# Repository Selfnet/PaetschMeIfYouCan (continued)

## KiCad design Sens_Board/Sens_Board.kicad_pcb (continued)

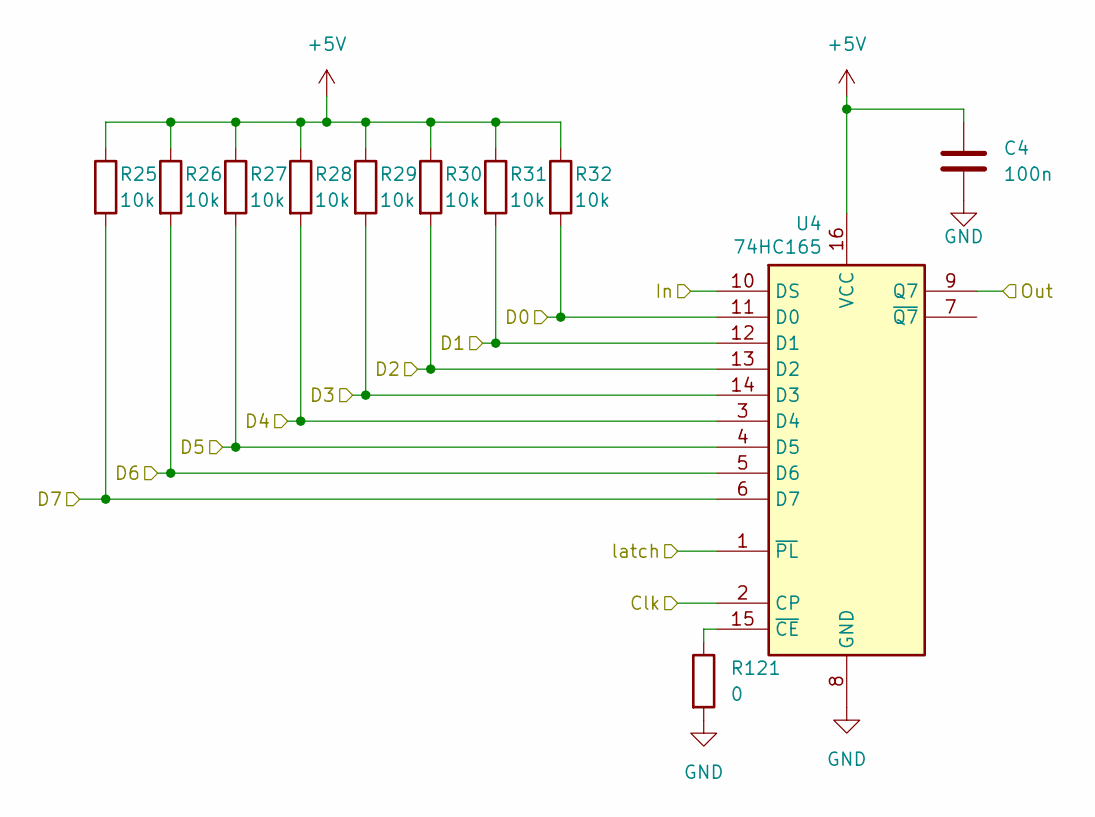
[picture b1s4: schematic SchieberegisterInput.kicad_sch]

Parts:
C4: 100n; C_0402_1005Metric
R25, R26, R27, R28, R29, R30, R31, R32: 10k; R_0402_1005Metric
R121: 0; R_0402_1005Metric
U4: 74HC165; SOIC-16_4.55x10.3mm_P1.27mm

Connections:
+5V: C4.1, R25.1, R26.1, R27.1, R28.1, R29.1, R30.1, R31.1, R32.1, U4.16 (VCC); also elsewhere on the board
/RJ45/SchieberegisterInput/D0: R32.2, U4.11 (D0); also elsewhere on the board
/RJ45/SchieberegisterInput/D1: R31.2, U4.12 (D1); also elsewhere on the board
/RJ45/SchieberegisterInput/D2: R30.2, U4.13 (D2); also elsewhere on the board
/RJ45/SchieberegisterInput/D3: R29.2, U4.14 (D3); also elsewhere on the board
/RJ45/SchieberegisterInput/D4: R28.2, U4.3 (D4); also elsewhere on the board
/RJ45/SchieberegisterInput/D5: R27.2, U4.4 (D5); also elsewhere on the board
/RJ45/SchieberegisterInput/D6: R26.2, U4.5 (D6); also elsewhere on the board
/RJ45/SchieberegisterInput/D7: R25.2, U4.6 (D7); also elsewhere on the board
/RJ45/SchieberegisterInput/Out: U4.9 (Q7); also elsewhere on the board
Data_Clk: U4.2 (CP); also elsewhere on the board
Data_Input: U4.10 (DS); also elsewhere on the board
Data_Latch: U4.1 (~PL); also elsewhere on the board
GND: C4.2, R121.2, U4.8 (GND); also elsewhere on the board
unnamed: R121.1, U4.15 (~CE)

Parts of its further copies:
C13, C22, C31, C40, C49, C58, C67, C76, C85, C94, C103: 100n; C_0402_1005Metric
R33, R34, R35, R36, R37, R38, R39, R40, R41, R42, R43, R44, R45, R46, R47, R48, R49, R50, R51, R52, R53, R54, R55, R56, R57, R58, R59, R60, R61, R62, R63, R64, R65, R66, R67, R68, R69, R70, R71, R72, R73, R74, R75, R76, R77, R78, R79, R80, R81, R82, R83, R84, R85, R86, R87, R88, R89, R90, R91, R92, R93, R94, R95, R96, R97, R98, R99, R100, R101, R102, R103, R104, R105, R106, R107, R108, R109, R110, R111, R112, R113, R114, R115, R116, R117, R118, R119, R120: 10k; R_0402_1005Metric
R122, R123, R124, R125, R126, R127, R128, R129, R130, R131, R132: 0; R_0402_1005Metric
U5, U6, U7, U8, U9, U10, U11, U12, U13, U14, U15: 74HC165; SOIC-16_4.55x10.3mm_P1.27mm

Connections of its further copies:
+5V: C13.1, C22.1, C31.1, C40.1, C49.1, C58.1, C67.1, C76.1, C85.1, C94.1, C103.1, R33.1, R34.1, R35.1, R36.1, R37.1, R38.1, R39.1, R40.1, R41.1, R42.1, R43.1, R44.1, R45.1, R46.1, R47.1, R48.1, R49.1, R50.1, R51.1, R52.1, R53.1, R54.1, R55.1, R56.1, R57.1, R58.1, R59.1, R60.1, R61.1, R62.1, R63.1, R64.1, R65.1, R66.1, R67.1, R68.1, R69.1, R70.1, R71.1, R72.1, R73.1, R74.1, R75.1, R76.1, R77.1, R78.1, R79.1, R80.1, R81.1, R82.1, R83.1, R84.1, R85.1, R86.1, R87.1, R88.1, R89.1, R90.1, R91.1, R92.1, R93.1, R94.1, R95.1, R96.1, R97.1, R98.1, R99.1, R100.1, R101.1, R102.1, R103.1, R104.1, R105.1, R106.1, R107.1, R108.1, R109.1, R110.1, R111.1, R112.1, R113.1, R114.1, R115.1, R116.1, R117.1, R118.1, R119.1, R120.1, U5.16 (VCC), U6.16 (VCC), U7.16 (VCC), U8.16 (VCC), U9.16 (VCC), U10.16 (VCC), U11.16 (VCC), U12.16 (VCC), U13.16 (VCC), U14.16 (VCC), U15.16 (VCC); also elsewhere on the board
/RJ45/SchieberegisterInput1/D0: R48.2, U5.11 (D0); also elsewhere on the board
/RJ45/SchieberegisterInput1/D1: R47.2, U5.12 (D1); also elsewhere on the board
/RJ45/SchieberegisterInput1/D2: R46.2, U5.13 (D2); also elsewhere on the board
/RJ45/SchieberegisterInput1/D3: R45.2, U5.14 (D3); also elsewhere on the board
/RJ45/SchieberegisterInput1/D4: R44.2, U5.3 (D4); also elsewhere on the board
/RJ45/SchieberegisterInput1/D5: R43.2, U5.4 (D5); also elsewhere on the board
/RJ45/SchieberegisterInput1/D6: R42.2, U5.5 (D6); also elsewhere on the board
/RJ45/SchieberegisterInput1/D7: R41.2, U5.6 (D7); also elsewhere on the board
/RJ45/SchieberegisterInput1/Out: U5.9 (Q7), U6.10 (DS)
/RJ45/SchieberegisterInput2/D0: R40.2, U6.11 (D0); also elsewhere on the board
/RJ45/SchieberegisterInput2/D1: R39.2, U6.12 (D1); also elsewhere on the board
/RJ45/SchieberegisterInput2/D2: R38.2, U6.13 (D2); also elsewhere on the board
/RJ45/SchieberegisterInput2/D3: R37.2, U6.14 (D3); also elsewhere on the board
/RJ45/SchieberegisterInput2/D4: R36.2, U6.3 (D4); also elsewhere on the board
/RJ45/SchieberegisterInput2/D5: R35.2, U6.4 (D5); also elsewhere on the board
/RJ45/SchieberegisterInput2/D6: R34.2, U6.5 (D6); also elsewhere on the board
/RJ45/SchieberegisterInput2/D7: R33.2, U6.6 (D7); also elsewhere on the board
/RJ45/SchieberegisterInput2/Out: U6.9 (Q7), U7.10 (DS)
/RJ45/SchieberegisterInput3/D0: R56.2, U7.11 (D0); also elsewhere on the board
/RJ45/SchieberegisterInput3/D1: R55.2, U7.12 (D1); also elsewhere on the board
/RJ45/SchieberegisterInput3/D2: R54.2, U7.13 (D2); also elsewhere on the board
/RJ45/SchieberegisterInput3/D3: R53.2, U7.14 (D3); also elsewhere on the board
/RJ45/SchieberegisterInput3/D4: R52.2, U7.3 (D4); also elsewhere on the board
/RJ45/SchieberegisterInput3/D5: R51.2, U7.4 (D5); also elsewhere on the board
/RJ45/SchieberegisterInput3/D6: R50.2, U7.5 (D6); also elsewhere on the board
/RJ45/SchieberegisterInput3/D7: R49.2, U7.6 (D7); also elsewhere on the board
/RJ45/SchieberegisterInput3/Out: U7.9 (Q7), U8.10 (DS)
/RJ45/SchieberegisterInput4/D0: R64.2, U8.11 (D0); also elsewhere on the board
/RJ45/SchieberegisterInput4/D1: R63.2, U8.12 (D1); also elsewhere on the board
/RJ45/SchieberegisterInput4/D2: R62.2, U8.13 (D2); also elsewhere on the board
/RJ45/SchieberegisterInput4/D3: R61.2, U8.14 (D3); also elsewhere on the board
/RJ45/SchieberegisterInput4/D4: R60.2, U8.3 (D4); also elsewhere on the board
/RJ45/SchieberegisterInput4/D5: R59.2, U8.4 (D5); also elsewhere on the board
/RJ45/SchieberegisterInput4/D6: R58.2, U8.5 (D6); also elsewhere on the board
/RJ45/SchieberegisterInput4/D7: R57.2, U8.6 (D7); also elsewhere on the board
/RJ45/SchieberegisterInput4/Out: U8.9 (Q7), U9.10 (DS)
/RJ45/SchieberegisterInput5/D0: R72.2, U9.11 (D0); also elsewhere on the board
/RJ45/SchieberegisterInput5/D1: R71.2, U9.12 (D1); also elsewhere on the board
/RJ45/SchieberegisterInput5/D2: R70.2, U9.13 (D2); also elsewhere on the board
/RJ45/SchieberegisterInput5/D3: R69.2, U9.14 (D3); also elsewhere on the board
/RJ45/SchieberegisterInput5/D4: R68.2, U9.3 (D4); also elsewhere on the board
/RJ45/SchieberegisterInput5/D5: R67.2, U9.4 (D5); also elsewhere on the board
/RJ45/SchieberegisterInput5/D6: R66.2, U9.5 (D6); also elsewhere on the board
/RJ45/SchieberegisterInput5/D7: R65.2, U9.6 (D7); also elsewhere on the board
/RJ45/SchieberegisterInput5/Out: U9.9 (Q7), U10.10 (DS)
/RJ45/SchieberegisterInput6/D0: R80.2, U10.11 (D0); also elsewhere on the board
/RJ45/SchieberegisterInput6/D1: R79.2, U10.12 (D1); also elsewhere on the board
/RJ45/SchieberegisterInput6/D2: R78.2, U10.13 (D2); also elsewhere on the board
/RJ45/SchieberegisterInput6/D3: R77.2, U10.14 (D3); also elsewhere on the board
/RJ45/SchieberegisterInput6/D4: R76.2, U10.3 (D4); also elsewhere on the board
/RJ45/SchieberegisterInput6/D5: R75.2, U10.4 (D5); also elsewhere on the board
/RJ45/SchieberegisterInput6/D6: R74.2, U10.5 (D6); also elsewhere on the board
/RJ45/SchieberegisterInput6/D7: R73.2, U10.6 (D7); also elsewhere on the board
/RJ45/SchieberegisterInput6/Out: U10.9 (Q7), U11.10 (DS)
/RJ45/SchieberegisterInput7/D0: R88.2, U11.11 (D0); also elsewhere on the board
/RJ45/SchieberegisterInput7/D1: R87.2, U11.12 (D1); also elsewhere on the board
/RJ45/SchieberegisterInput7/D2: R86.2, U11.13 (D2); also elsewhere on the board
/RJ45/SchieberegisterInput7/D3: R85.2, U11.14 (D3); also elsewhere on the board
/RJ45/SchieberegisterInput7/D4: R84.2, U11.3 (D4); also elsewhere on the board
/RJ45/SchieberegisterInput7/D5: R83.2, U11.4 (D5); also elsewhere on the board
/RJ45/SchieberegisterInput7/D6: R82.2, U11.5 (D6); also elsewhere on the board
/RJ45/SchieberegisterInput7/D7: R81.2, U11.6 (D7); also elsewhere on the board
/RJ45/SchieberegisterInput7/Out: U11.9 (Q7), U12.10 (DS)
/RJ45/SchieberegisterInput8/D0: R96.2, U12.11 (D0); also elsewhere on the board
/RJ45/SchieberegisterInput8/D1: R95.2, U12.12 (D1); also elsewhere on the board
/RJ45/SchieberegisterInput8/D2: R94.2, U12.13 (D2); also elsewhere on the board
/RJ45/SchieberegisterInput8/D3: R93.2, U12.14 (D3); also elsewhere on the board
/RJ45/SchieberegisterInput8/D4: R92.2, U12.3 (D4); also elsewhere on the board
/RJ45/SchieberegisterInput8/D5: R91.2, U12.4 (D5); also elsewhere on the board
/RJ45/SchieberegisterInput8/D6: R90.2, U12.5 (D6); also elsewhere on the board
/RJ45/SchieberegisterInput8/D7: R89.2, U12.6 (D7); also elsewhere on the board
/RJ45/SchieberegisterInput8/Out: U12.9 (Q7), U13.10 (DS)
/RJ45/SchieberegisterInput9/D0: R104.2, U13.11 (D0); also elsewhere on the board
/RJ45/SchieberegisterInput9/D1: R103.2, U13.12 (D1); also elsewhere on the board
/RJ45/SchieberegisterInput9/D2: R102.2, U13.13 (D2); also elsewhere on the board
/RJ45/SchieberegisterInput9/D3: R101.2, U13.14 (D3); also elsewhere on the board
/RJ45/SchieberegisterInput9/D4: R100.2, U13.3 (D4); also elsewhere on the board
/RJ45/SchieberegisterInput9/D5: R99.2, U13.4 (D5); also elsewhere on the board
/RJ45/SchieberegisterInput9/D6: R98.2, U13.5 (D6); also elsewhere on the board
/RJ45/SchieberegisterInput9/D7: R97.2, U13.6 (D7); also elsewhere on the board
/RJ45/SchieberegisterInput10/D0: R112.2, U14.11 (D0); also elsewhere on the board
/RJ45/SchieberegisterInput10/D1: R111.2, U14.12 (D1); also elsewhere on the board
/RJ45/SchieberegisterInput10/D2: R110.2, U14.13 (D2); also elsewhere on the board
/RJ45/SchieberegisterInput10/D3: R109.2, U14.14 (D3); also elsewhere on the board
/RJ45/SchieberegisterInput10/D4: R108.2, U14.3 (D4); also elsewhere on the board
/RJ45/SchieberegisterInput10/D5: R107.2, U14.4 (D5); also elsewhere on the board
/RJ45/SchieberegisterInput10/D6: R106.2, U14.5 (D6); also elsewhere on the board
/RJ45/SchieberegisterInput10/D7: R105.2, U14.6 (D7); also elsewhere on the board
/RJ45/SchieberegisterInput10/In: U13.9 (Q7), U14.10 (DS)
/RJ45/SchieberegisterInput10/Out: U14.9 (Q7), U15.10 (DS)
/RJ45/SchieberegisterInput11/D0: R120.2, U15.11 (D0); also elsewhere on the board
/RJ45/SchieberegisterInput11/D1: R119.2, U15.12 (D1); also elsewhere on the board
/RJ45/SchieberegisterInput11/D2: R118.2, U15.13 (D2); also elsewhere on the board
/RJ45/SchieberegisterInput11/D3: R117.2, U15.14 (D3); also elsewhere on the board
/RJ45/SchieberegisterInput11/D4: R116.2, U15.3 (D4); also elsewhere on the board
/RJ45/SchieberegisterInput11/D5: R115.2, U15.4 (D5); also elsewhere on the board
/RJ45/SchieberegisterInput11/D6: R114.2, U15.5 (D6); also elsewhere on the board
/RJ45/SchieberegisterInput11/D7: R113.2, U15.6 (D7); also elsewhere on the board
/RJ45/SchieberegisterInput/Out: U5.10 (DS); also elsewhere on the board
Data_Clk: U5.2 (CP), U6.2 (CP), U7.2 (CP), U8.2 (CP), U9.2 (CP), U10.2 (CP), U11.2 (CP), U12.2 (CP), U13.2 (CP), U14.2 (CP), U15.2 (CP); also elsewhere on the board
Data_Latch: U5.1 (~PL), U6.1 (~PL), U7.1 (~PL), U8.1 (~PL), U9.1 (~PL), U10.1 (~PL), U11.1 (~PL), U12.1 (~PL), U13.1 (~PL), U14.1 (~PL), U15.1 (~PL); also elsewhere on the board
Data_Output: U15.9 (Q7); also elsewhere on the board
GND: C13.2, C22.2, C31.2, C40.2, C49.2, C58.2, C67.2, C76.2, C85.2, C94.2, C103.2, R122.2, R123.2, R124.2, R125.2, R126.2, R127.2, R128.2, R129.2, R130.2, R131.2, R132.2, U5.8 (GND), U6.8 (GND), U7.8 (GND), U8.8 (GND), U9.8 (GND), U10.8 (GND), U11.8 (GND), U12.8 (GND), U13.8 (GND), U14.8 (GND), U15.8 (GND); also elsewhere on the board
unnamed: R123.1, U5.15 (~CE)
unnamed: R122.1, U6.15 (~CE)
unnamed: R124.1, U7.15 (~CE)
unnamed: R125.1, U8.15 (~CE)
unnamed: R126.1, U9.15 (~CE)
unnamed: R127.1, U10.15 (~CE)
unnamed: R128.1, U11.15 (~CE)
unnamed: R129.1, U12.15 (~CE)
unnamed: R130.1, U13.15 (~CE)
unnamed: R131.1, U14.15 (~CE)
unnamed: R132.1, U15.15 (~CE)

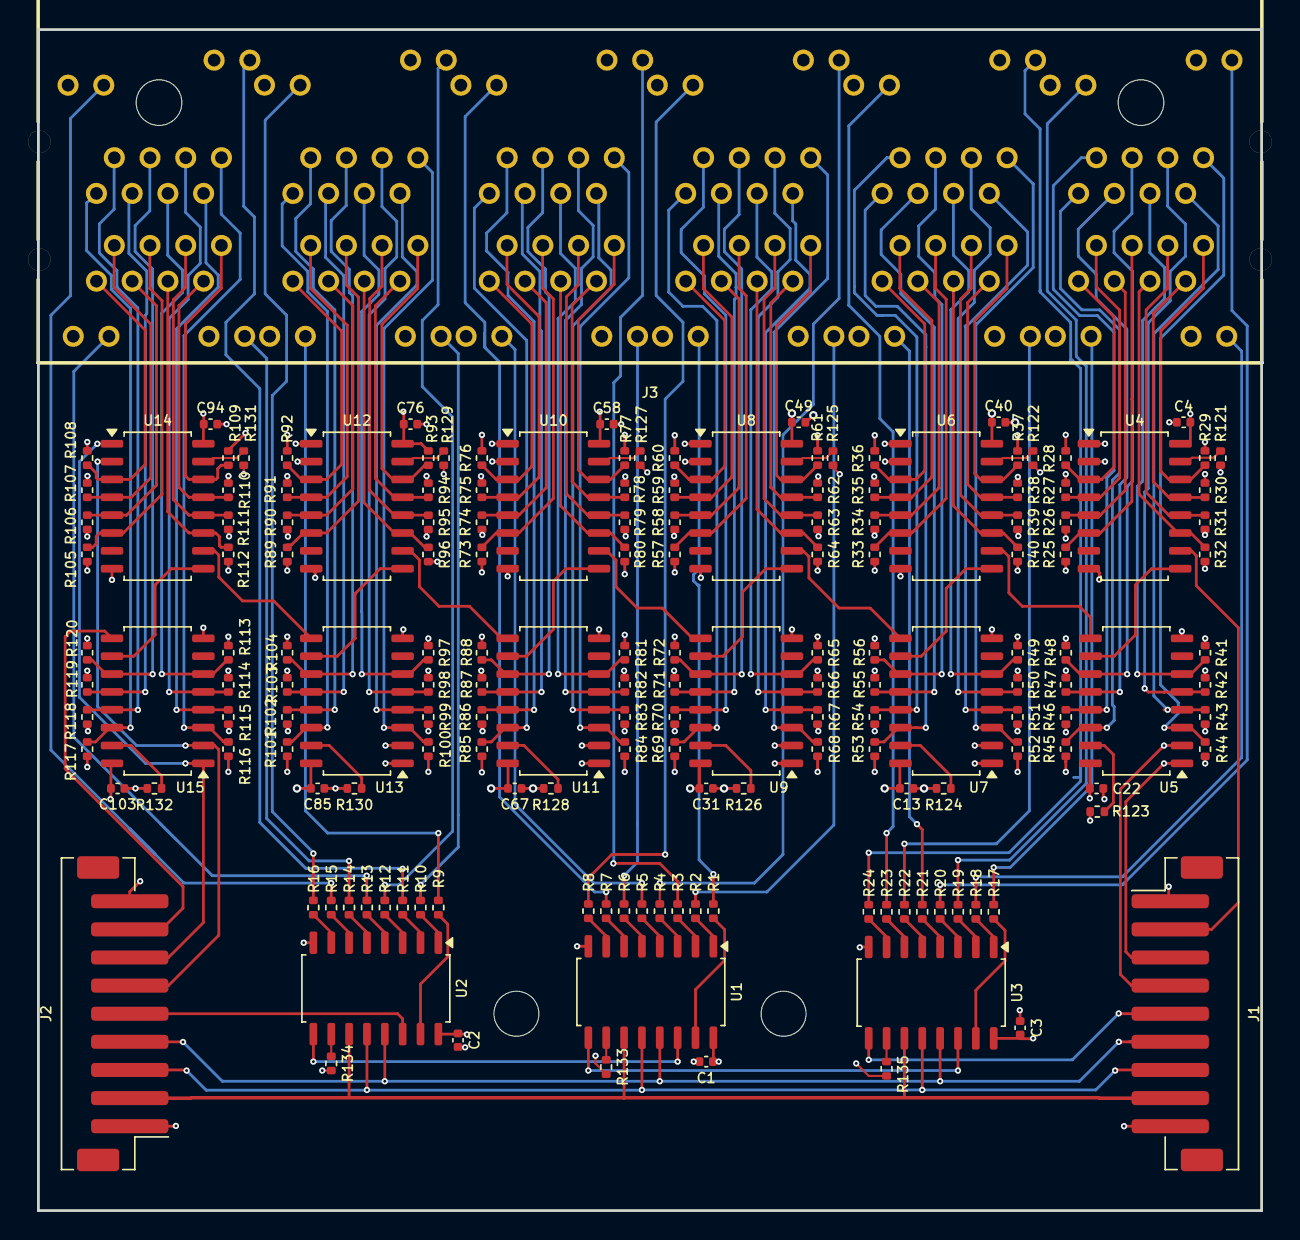
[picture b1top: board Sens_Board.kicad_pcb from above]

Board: 4 copper layers, 87.0 x 84.0 mm, 170 parts (0 on the bottom side), 183 nets.

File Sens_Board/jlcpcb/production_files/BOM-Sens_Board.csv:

Comment,Designator,Footprint,LCSC,Quantity
0,"R121,R122,R123,R124,R125,R126,R127,R128,R129,R130,R131,R132,R133,R134,R135",R_0402_1005Metric,C17168,15
100n,"C1,C103,C13,C2,C22,C3,C31,C4,C40,C49,C58,C67,C76,C85,C94",C_0402_1005Metric,C1525,15
10k,"R100,R101,R102,R103,R104,R105,R106,R107,R108,R109,R110,R111,R112,R113,R114,R115,R116,R117,R118,R119,R120,R25,R26,R27,R28,R29,R30,R31,R32,R33,R34,R35,R36,R37,R38,R39,R40,R41,R42,R43,R44,R45,R46,R47,R48,R49,R50,R51,R52,R53,R54,R55,R56,R57,R58,R59,R60,R61,R62,R63,R64,R65,R66,R67,R68,R69,R70,R71,R72,R73,R74,R75,R76,R77,R78,R79,R80,R81,R82,R83,R84,R85,R86,R87,R88,R89,R90,R91,R92,R93,R94,R95,R96,R97,R98,R99",R_0402_1005Metric,C25744,96
120,"R1,R10,R11,R12,R13,R14,R15,R16,R17,R18,R19,R2,R20,R21,R22,R23,R24,R3,R4,R5,R6,R7,R8,R9",R_0402_1005Metric,C25079,24
74HC165,"U10,U11,U12,U13,U14,U15,U4,U5,U6,U7,U8,U9",SOIC-16_4.55x10.3mm_P1.27mm,C5613,12
74HC595,"U1,U2,U3",SOIC-16_4.55x10.3mm_P1.27mm,C5947,3
Conn_01x09_Pin,"J1,J2",JST_PH_B9B-PH-SM4-TB_1x09-1MP_P2.00mm_Vertical,C5175301,2
~,J3,RJ45-TH_RJ45-TH_HC-RJ45-059D-2X6-2-04,C46261622,1

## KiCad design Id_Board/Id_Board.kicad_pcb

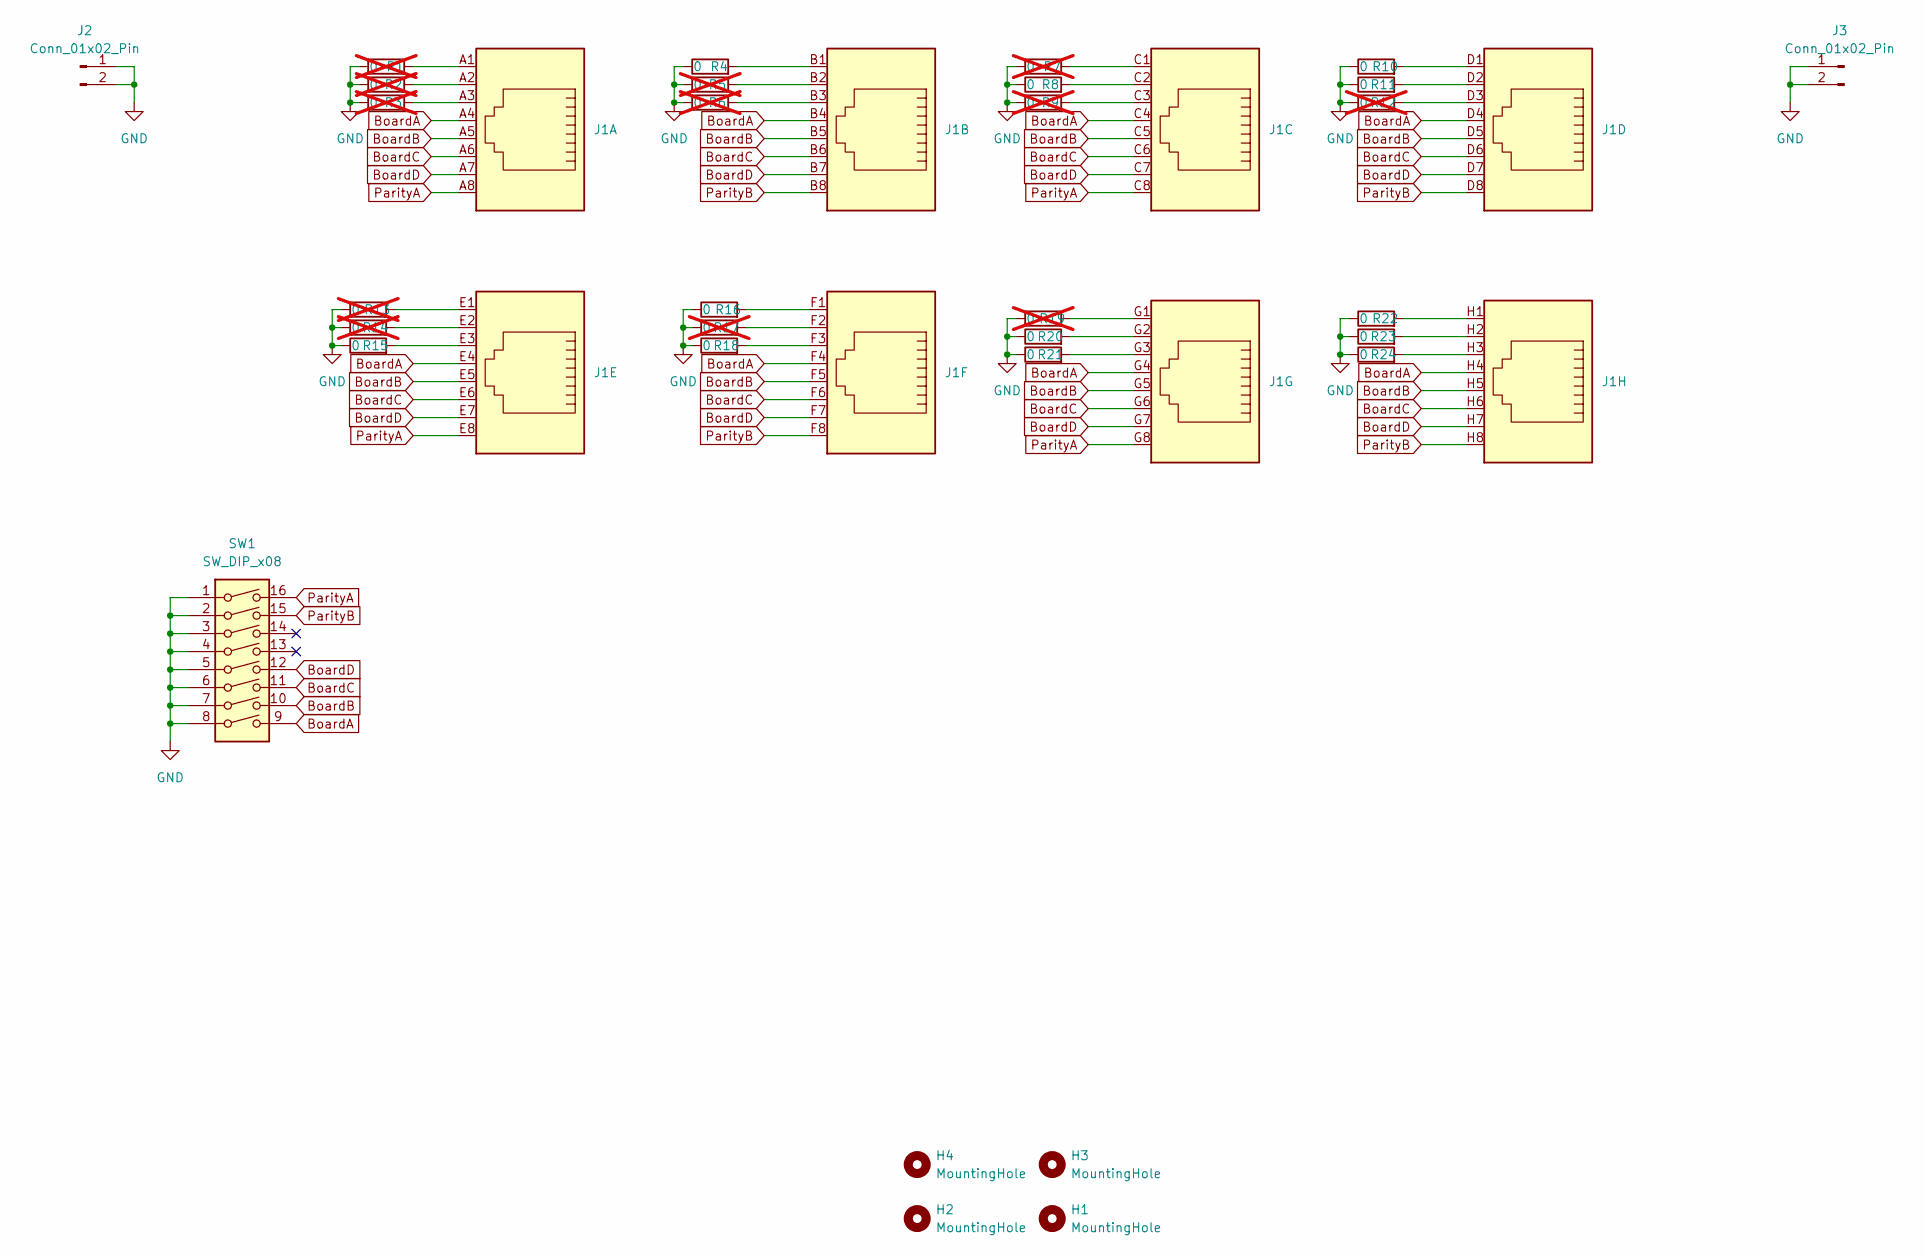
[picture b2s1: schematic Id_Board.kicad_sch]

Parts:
H1, H2, H3, H4: MountingHole; MountingHole_3.2mm_M3
J1: RJ45-TH_HC-WK88-H13-1X8-55QS_1
J2, J3: Conn_01x02_Pin; JST_PH_B2B-PH-SM4-TB_1x02-1MP_P2.00mm_Vertical
R1, R2, R3, R5, R6, R7, R9, R12, R13, R14, R17, R19: 0; R_0603_1608Metric; not fitted
R4, R8, R10, R11, R15, R16, R18, R20, R21, R22, R23, R24: 0; R_0603_1608Metric
SW1: SW_DIP_x08; SW-SMD_16P-L20.3-W6.0-P2.54-LS9.3-BL

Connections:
BoardA: J1.A4, J1.B4, J1.C4, J1.D4, J1.E4, J1.F4, J1.G4, J1.H4, SW1.9
BoardB: J1.A5, J1.B5, J1.C5, J1.D5, J1.E5, J1.F5, J1.G5, J1.H5, SW1.10
BoardC: J1.A6, J1.B6, J1.C6, J1.D6, J1.E6, J1.F6, J1.G6, J1.H6, SW1.11
BoardD: J1.A7, J1.B7, J1.C7, J1.D7, J1.E7, J1.F7, J1.G7, J1.H7, SW1.12
GND: J2.1, J2.2, J3.1, J3.2, R1.1, R2.1, R3.1, R4.1, R5.1, R6.1, R7.1, R8.1, R9.1, R10.1, R11.1, R12.1, R13.1, R14.1, R15.1, R16.1, R17.1, R18.1, R19.1, R20.1, R21.1, R22.1, R23.1, R24.1, SW1.1, SW1.2, SW1.3, SW1.4, SW1.5, SW1.6, SW1.7, SW1.8
unnamed: J1.A1, R1.2
unnamed: J1.A2, R2.2
unnamed: J1.A3, R3.2
unnamed: J1.B1, R4.2
unnamed: J1.B2, R5.2
unnamed: J1.B3, R6.2
unnamed: J1.C1, R7.2
unnamed: J1.C2, R8.2
unnamed: J1.C3, R9.2
unnamed: J1.D1, R10.2
unnamed: J1.D2, R11.2
unnamed: J1.D3, R12.2
unnamed: J1.E1, R13.2
unnamed: J1.E2, R14.2
unnamed: J1.E3, R15.2
unnamed: J1.F1, R16.2
unnamed: J1.F2, R17.2
unnamed: J1.F3, R18.2
unnamed: J1.G1, R19.2
unnamed: J1.G2, R20.2
unnamed: J1.G3, R21.2
unnamed: J1.H1, R22.2
unnamed: J1.H2, R23.2
unnamed: J1.H3, R24.2
ParityA: J1.A8, J1.C8, J1.E8, J1.G8, SW1.16
ParityB: J1.B8, J1.D8, J1.F8, J1.H8, SW1.15

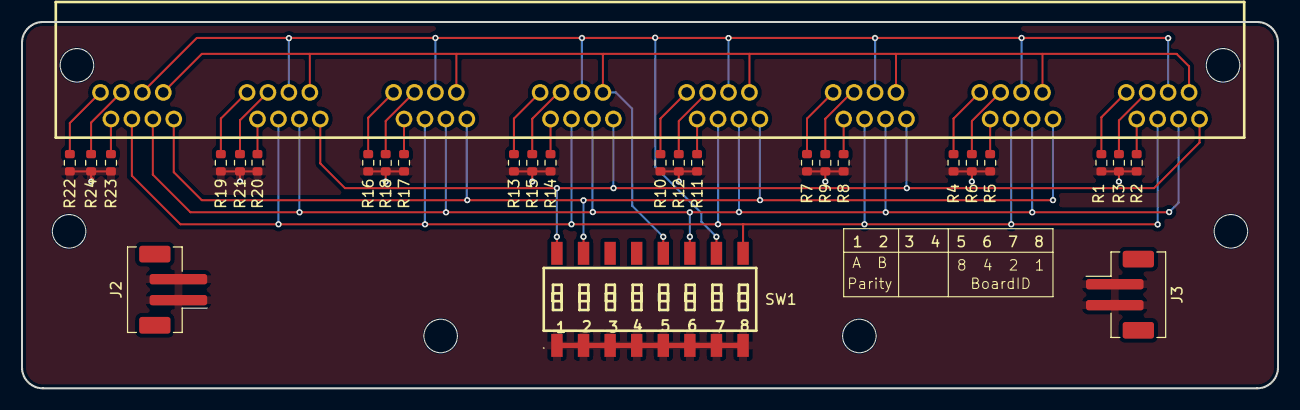
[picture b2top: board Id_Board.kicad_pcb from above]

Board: 2 copper layers, 120.0 x 35.0 mm, 32 parts (0 on the bottom side), 31 nets.

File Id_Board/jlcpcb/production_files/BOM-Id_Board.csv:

Comment,Designator,Footprint,LCSC,Quantity
0,"R10,R11,R15,R16,R18,R20,R21,R22,R23,R24,R4,R8",R_0603_1608Metric,C21189,12
Conn_01x02_Pin,"J2,J3",JST_PH_B2B-PH-SM4-TB_1x02-1MP_P2.00mm_Vertical,C2936227,2
SW_DIP_x08,SW1,SW-SMD_16P-L20.3-W6.0-P2.54-LS9.3-BL,C5145016,1
~,J1,RJ45-TH_HC-WK88-H13-1X8-55QS_1,C7501829,1

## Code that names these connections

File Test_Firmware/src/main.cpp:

#include <Arduino.h>

static const int PIN_LED_CLK    = 14;
static const int PIN_LED_LATCH  = 13;
static const int PIN_LED_OE     = 10;  // active low
static const int PIN_LED_DOUT   = 15;
static const int PIN_DATA_CLK   = 18;
static const int PIN_DATA_LATCH = 17;
static const int PIN_DATA_DIN   = 16;

static const int NUM_PORTS = 48;

static const int NUM_PORTS_PER_BANK = 12;
static const int NUM_LEDS = NUM_PORTS * 2;
static const size_t NUM_LED_BYTES = (NUM_LEDS + 7) / 8;

uint8_t ledData[NUM_LED_BYTES] = {0};
uint8_t portData[NUM_PORTS] = {0};



static const uint8_t ledIdxMapping[] = {
  // Y,  G
     1,  0,     // Port 0
     3,  2,
     5,  4,
     7,  6,
     9,  8, 
    11, 15,     // Port 5 (green swapped with yellow of port 7)
    13, 12,
    10, 14,     // Port 7 (yellow swapped with green of port 5)
    17, 16,
    19, 23,     // Port 9 (green swapped with yellow of port 11)
    21, 20,
    18, 22,     // Port 11 (yellow swapped with green of port 9)
};


void updateLeds() {
    for (int i = 0; i < NUM_LED_BYTES; i++) {
        shiftOut(PIN_LED_DOUT, PIN_LED_CLK, MSBFIRST, ledData[i]);
    }
    digitalWrite(PIN_LED_LATCH, LOW);
    digitalWrite(PIN_LED_LATCH, HIGH);
}

// led: 0 = yellow, 1 = green
void setLed(int port, int led, bool state) {
    int ledIdx = port * 2 + led;
    int portBankOffset = (ledIdx / 2 / NUM_PORTS_PER_BANK) * NUM_PORTS_PER_BANK * 2;
    int mappedIdx = ledIdxMapping[ledIdx % (NUM_PORTS_PER_BANK*2)] + portBankOffset;

    if (state) {
        ledData[mappedIdx / 8] |= 1 << (mappedIdx % 8);
    }
    else {
        ledData[mappedIdx / 8] &= ~(1 << (mappedIdx % 8));
    }
}


void setup() {
    pinMode(PIN_LED_CLK, OUTPUT);
    pinMode(PIN_LED_LATCH, OUTPUT);
    digitalWrite(PIN_LED_OE, HIGH);
    pinMode(PIN_LED_OE, OUTPUT);
    pinMode(PIN_LED_DOUT, OUTPUT);
    pinMode(PIN_DATA_CLK, OUTPUT);
    digitalWrite(PIN_DATA_CLK, HIGH);
    pinMode(PIN_DATA_LATCH, OUTPUT);

    analogWrite(PIN_LED_OE, 127);

    Serial.begin(115200);

    for (int i = 0; i < NUM_LEDS; i++) {
        memset(ledData, 0, sizeof(ledData));
        setLed(i/2, i%2, 1);
        updateLeds();
        delay(25);
    }
    memset(ledData, 0, sizeof(ledData));
    updateLeds();
}


uint32_t ledIdx = 0;

void loop() {
    ledIdx++;
    if (ledIdx >= NUM_LEDS) {
        ledIdx = 0;
    }
    
    memset(ledData, 0, sizeof(ledData));
    updateLeds();

    digitalWrite(PIN_DATA_LATCH, LOW);
    digitalWrite(PIN_DATA_LATCH, HIGH);
    for (int i = 0; i < NUM_PORTS; i++) {
        // portData[i] = shiftIn(PIN_DATA_DIN, PIN_DATA_CLK, MSBFIRST);
        // Serial.print(portData[i], 2);
        // Serial.print(" ");

        portData[i] = 0;
        for (int bit = 0; bit < 8; bit++) {
            portData[i] |= digitalRead(PIN_DATA_DIN) << bit;
            digitalWrite(PIN_DATA_CLK, LOW);
            digitalWrite(PIN_DATA_CLK, HIGH);
        }

        if (portData[i] != 0xFF) {
            setLed(NUM_PORTS - i - 1, 0, (ledIdx % 2));
            setLed(NUM_PORTS - i - 1, 1, !(ledIdx % 2));
            updateLeds();
        }

        char buf[64];
        int len = snprintf(buf, sizeof(buf), "%02X ", portData[i]);
        Serial.write(buf, len);
    }
    Serial.println();


    delay(100);
}

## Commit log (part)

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2026-04-29 add Boards
2026-04-30 finished IdBoard
2026-04-30 Senssoard Firsat LAyout start
2026-05-01 set Komponents SensorBoard
2026-05-05 finish SensBoard
2026-05-05 add pull UP/DOWN
2026-05-05 fixes and optmierung
2026-05-05 Production File generate
2026-05-05 prettify silkscreen
2026-05-08 update production files
2026-05-08 add production files ID board
2026-05-08 add .csv
2026-05-08 add production files Sens
2026-05-08 update Cnumbers
2026-05-08 update JST Economic
2026-05-21 add test firmware
2026-05-21 Test Firmware: Maybe add bootup animation
2026-05-22 Test Firmware: extend to multiple port banks
2026-05-28 add Mechanic Files
2026-06-02 Add POC webserver
2026-06-08 chore(ui): vendor socket.io client
2026-06-08 feat(server): sync clock state safely
2026-06-08 chore: ignore local env files
2026-06-08 feat(ui): add race dashboard
2026-06-28 Add ability to verify
    Also add:
    - Remove Right and Left Player icon, players are 1 and 2
    - Add V and S keys for toggling verify and restarting the serial threads
    - Rename Paused to Stopped
    This intentionally leaves the topic of miliseconds open
2026-06-29 Update index.html
    Fix typo
